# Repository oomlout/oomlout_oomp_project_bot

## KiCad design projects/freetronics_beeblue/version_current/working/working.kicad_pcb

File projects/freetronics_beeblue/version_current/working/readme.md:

# BeeBlue by freetronics  
This is a harvested standardized copy of a project from github.  
The original project can be found at:  
https://github.com/freetronics/BeeBlue  
Please consult that link for additional, details, files, and license information.  
Note: It was auto harvested and if the original repo had more than one board file or anything out of the ordinary the files here are likely not representative.

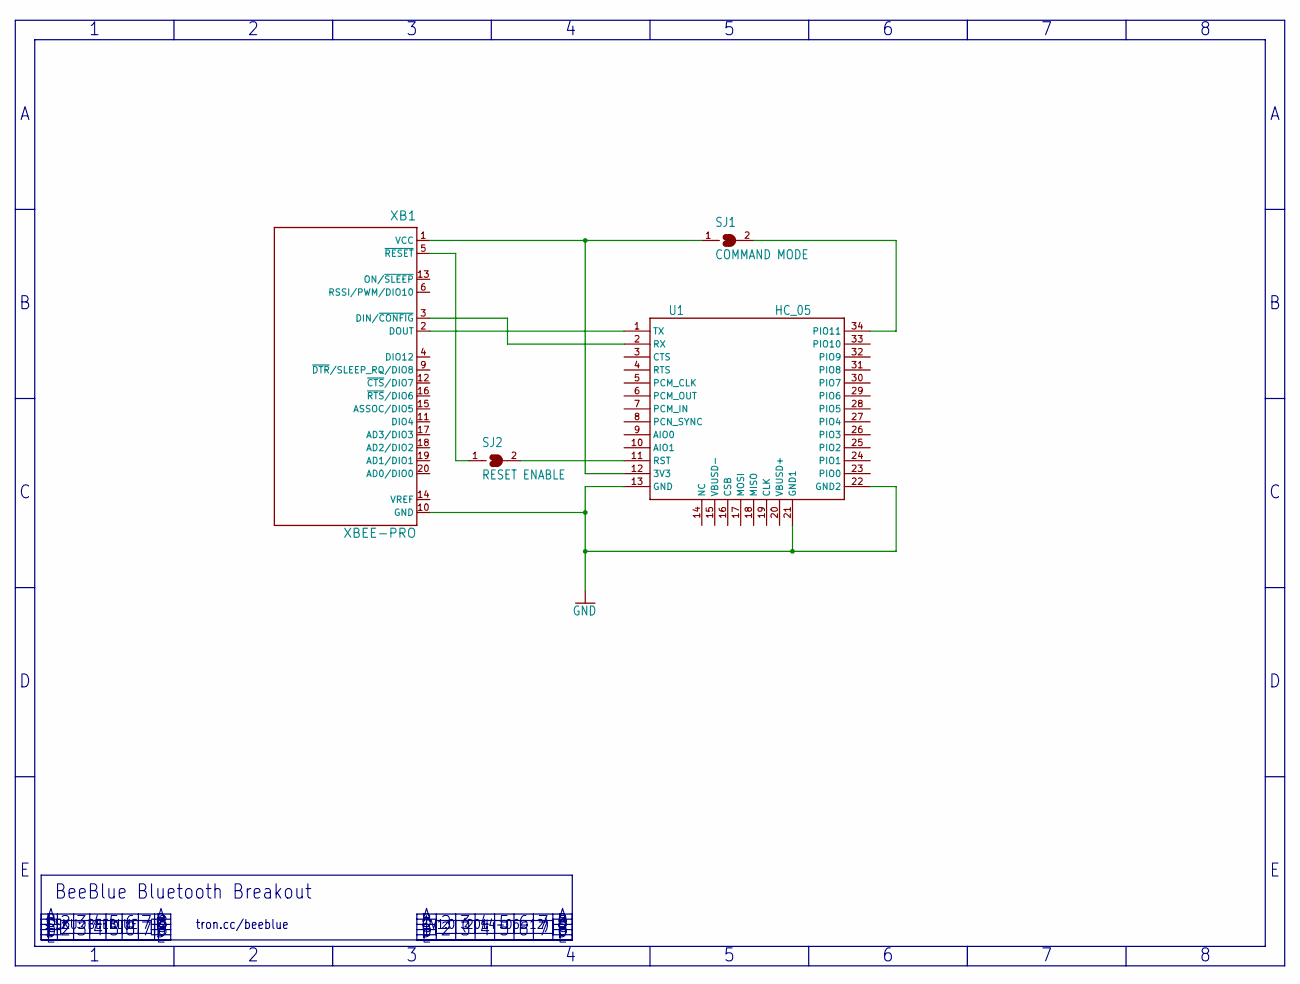
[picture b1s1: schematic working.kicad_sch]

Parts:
SJ1: COMMAND MODE; SJ
SJ2: RESET ENABLE; SJ
U1: HC_05; BLUETOOTH_SMD
XB1: XBEE-PRO

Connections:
GND: U1.13 (GND), U1.21 (GND1), U1.22 (GND2), XB1.10 (GND)
unnamed: SJ1.2, U1.34 (PIO11)
unnamed: U1.1 (TX), XB1.2 (DOUT)
unnamed: U1.2 (RX), XB1.3 (DIN/~CONFIG)
unnamed: SJ1.1, U1.12 (3V3), XB1.1 (VCC)
unnamed: SJ2.2, U1.11 (RST)
unnamed: SJ2.1, XB1.5 (~RESET)

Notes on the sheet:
tron.cc/beeblue
SKU: BEEBLUE
BeeBlue Bluetooth Breakout
V1.0 (2014-06-12)

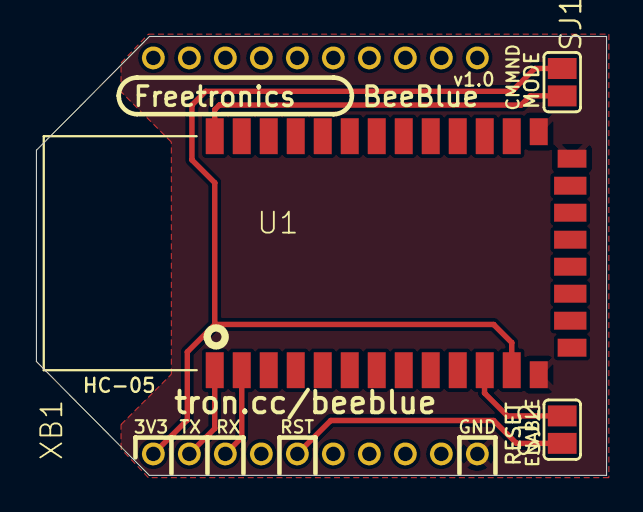
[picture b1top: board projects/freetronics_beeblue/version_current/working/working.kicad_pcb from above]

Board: 2 copper layers, 31.7 x 24.4 mm, 4 parts (0 on the bottom side), 7 nets.

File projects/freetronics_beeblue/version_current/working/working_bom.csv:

"Id";"Designator";"Footprint";"Quantity";"Designation";"Supplier and ref";
1;"XB1";"XBEE-PRO";1;"XBEE-PRO";;;
2;"U1";"BLUETOOTH_SMD";1;"HC_05";;;
3;"SJ2";"SJ";1;"RESET ENABLE";;;
4;"SJ1";"SJ";1;"COMMAND MODE";;;

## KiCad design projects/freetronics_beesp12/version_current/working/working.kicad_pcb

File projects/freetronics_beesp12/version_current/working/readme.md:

# OOMP Project  
## BEESP12  by freetronics  
  
oomp key: oomp_projects_flat_freetronics_beesp12  
(snippet of original readme)  

  full source readme at [readme_src.md](readme_src.md)  
  
source repo at: [https://github.com/freetronics/BEESP12](https://github.com/freetronics/BEESP12)  
## Board  

## Schematic  

[schematic pdf](working_schematic.pdf)  
## Images

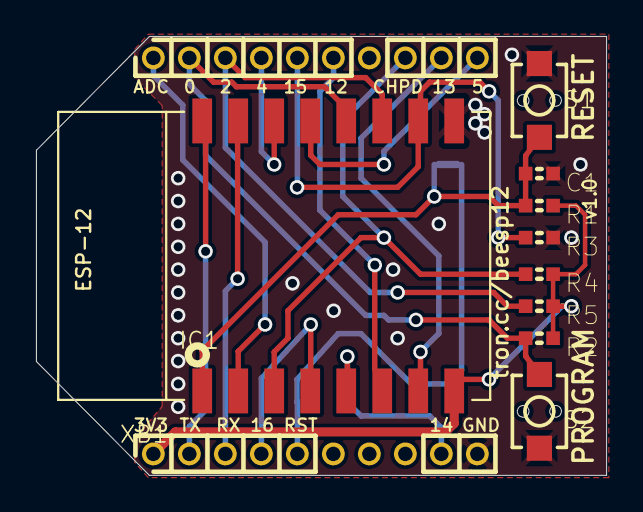
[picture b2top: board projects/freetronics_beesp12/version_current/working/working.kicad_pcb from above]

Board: 2 copper layers, 31.7 x 24.4 mm, 11 parts (1 on the bottom side), 17 nets.

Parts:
C1: 100nF; 0603
IC1: ESP12
R1, R3, R4, R5: 22K; 0603
R2: 22k; 0603
S1: RESET; TACTILE_SWITCH_SMD_2PIN_TINY
S2: PROGRAM; TACTILE_SWITCH_SMD_2PIN_TINY
SJ2: RESET LINK; SJC
XB1: XBEE-PRO

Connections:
3.3V: IC1.8, R1.2, R2.2, R4.2, R5.2, XB1.1
ADC: IC1.2, XB1.20
CH_PD: IC1.3, R4.1, XB1.13
GND: C1.2, IC1.9, R3.1, S1.2, S2.2, XB1.10
GPIO0: IC1.12, R2.1, S2.1, XB1.19
GPIO2: IC1.11, R5.1, XB1.18
GPIO4: IC1.14, XB1.17
GPIO5: IC1.13, XB1.11
GPIO12: IC1.6, XB1.15
GPIO13: IC1.7, XB1.12
GPIO14: IC1.5, XB1.9
GPIO15: IC1.10, R3.2, XB1.16
GPIO16: IC1.4, XB1.4
unnamed: C1.1, IC1.1, R1.1, S1.1, SJ2.2
RESET: SJ2.1, XB1.5
RXD: IC1.15, XB1.3
TXD: IC1.16, XB1.2

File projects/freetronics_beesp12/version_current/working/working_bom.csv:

"Id";"Designator";"Footprint";"Quantity";"Designation";"Supplier and ref";
1;"C1";"0603";1;"100nF";;;
2;"R1,R4,R5,R3";"0603";4;"22K";;;
3;"R2";"0603";1;"22k";;;
4;"S1";"TACTILE_SWITCH_SMD_2PIN_TINY";1;"RESET";;;
5;"S2";"TACTILE_SWITCH_SMD_2PIN_TINY";1;"PROGRAM";;;
6;"XB1";"XBEE-PRO";1;"XBEE-PRO";;;
7;"IC1";"ESP12";1;"ESP12";;;
8;"SJ2";"SJC";1;"RESET LINK";;;

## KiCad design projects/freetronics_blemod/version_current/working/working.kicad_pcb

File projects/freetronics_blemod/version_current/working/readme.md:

# BLEMod by freetronics  
This is a harvested standardized copy of a project from github.  
The original project can be found at:  
https://github.com/freetronics/BLEMod  
Please consult that link for additional, details, files, and license information.  
Note: It was auto harvested and if the original repo had more than one board file or anything out of the ordinary the files here are likely not representative.

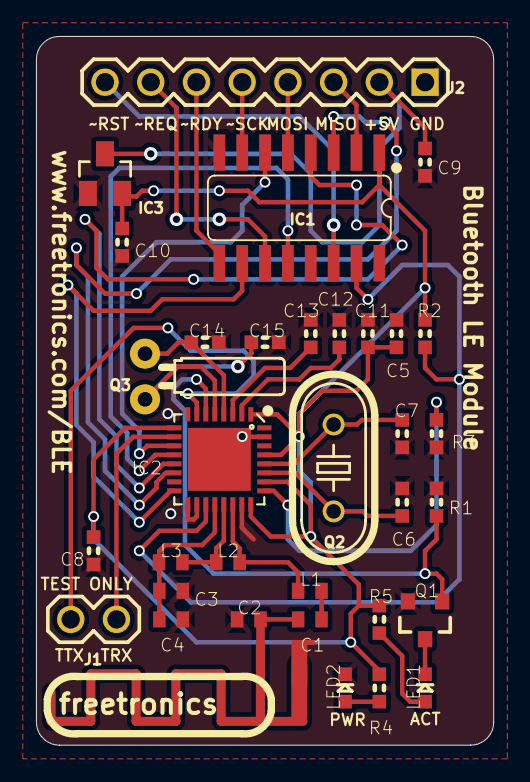
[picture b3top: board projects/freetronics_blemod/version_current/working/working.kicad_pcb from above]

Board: 2 copper layers, 25.4 x 39.4 mm, 34 parts (0 on the bottom side), 33 nets.

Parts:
ANT1: ANTENNA; RN-ANT
C1: 1.8pF; C0402
C2: 1.2pF; C0402
C3: NP; C0402
C4: 2.2nF; C0402
C5: 1nF; 0603
C6, C7: 27pF; 0603
C8, C11, C12: 100nF; 0603
C9, C10: 1µF; 0603
C13: 33nF; 0603
C14, C15: 18pF; 0603
IC1: HEF4050BT; SO16
IC2: NRF8001; FITNESSDEVICE_QFN-32
IC3: MCP1700T-3002E; SOT23
J1: Debug/Test UART; 1X02
J2: Interface; 1X08
L1: 3.9nH; C0402
L2: 8.2nH; C0402
L3: 5.6nH; C0402
LED1: Activity; LED-0603
LED2: Power; LED-0603
Q1: 2N7002; SOT23-3
Q2: 16 MHz; HC49U-V
Q3: 32768 Hz; TC26H
R1: 100kΩ; 0603
R2: 10kΩ; 0603
R3: 22kΩ 1%; 0603
R4, R5: 1kΩ; 0603

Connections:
+3.0V: C5.2, C8.2, C10.2, C11.2, IC1.1, IC2.1, IC2.9, IC2.24, IC2.26, IC2.29, IC3.2, R2.1, R4.2, R5.1
+5V: C9.2, IC3.3, J2.2
ACTIVE: IC2.6, Q1.1, R1.1
ANT1: IC2.21, L2.2, L3.1
ANT2: IC2.22, L1.2, L2.1
GND: ANT1.GND, C2.1, C3.1, C4.1, C5.1, C6.1, C7.1, C8.1, C9.1, C10.1, C11.1, C12.1, C13.1, C14.1, C15.1, IC1.8, IC2.8, IC2.17, IC2.18, IC2.23, IC2.30, IC2.31, IC2.EP, IC3.1, J2.1, LED2.C, Q1.2, R1.2, R3.2
MISO: IC1.3, IC2.14
MISO_5V: IC1.2, J2.3
MOSI: IC1.4, IC2.13
MOSI_5V: IC1.5, J2.4
unnamed: C12.2, IC2.2
unnamed: C13.2, IC2.3
unnamed: IC2.25, R3.1
unnamed: C7.2, IC2.28, Q2.1
unnamed: C6.2, IC2.27, Q2.2
unnamed: C14.2, IC2.4, Q3.1
unnamed: C15.2, IC2.5, Q3.2
unnamed: ANT1.FEED, C1.1, C2.2
unnamed: C1.2, L1.1
unnamed: LED2.A, R4.1
unnamed: LED1.C, Q1.3
unnamed: LED1.A, R5.2
RXD: IC2.10, J1.1
SCK: IC1.6, IC2.11
SCK_5V: IC1.7, J2.5
TXD: IC2.7, J1.2
VDD_PA: C3.2, C4.2, IC2.20, L3.2
~RDY_5V: IC1.9, J2.6
~RDY: IC1.10, IC2.16
~REQ_5V: IC1.11, J2.7
~REQ: IC1.12, IC2.12
~RESET_5V: IC1.14, J2.8
~RESET: IC1.15, IC2.19, R2.2

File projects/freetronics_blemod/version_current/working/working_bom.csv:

"Id";"Designator";"Footprint";"Quantity";"Designation";"Supplier and ref";
1;"J2";"1X08";1;"Interface";;;
2;"C13";"0603";1;"33nF";;;
3;"C8,C12,C11";"0603";3;"100nF";;;
4;"Q1";"SOT23-3";1;"2N7002";;;
5;"C9,C10";"0603";2;"1µF";;;
6;"C2";"C0402";1;"1.2pF";;;
7;"C5";"0603";1;"1nF";;;
8;"LED1";"LED-0603";1;"Activity";;;
9;"R4,R5";"0603";2;"1kΩ";;;
10;"IC2";"FITNESSDEVICE_QFN-32";1;"NRF8001";;;
11;"C1";"C0402";1;"1.8pF";;;
12;"C4";"C0402";1;"2.2nF";;;
13;"R1";"0603";1;"100kΩ";;;
14;"Q3";"TC26H";1;"32768 Hz";;;
15;"IC3";"SOT23";1;"MCP1700T-3002E";;;
16;"C3";"C0402";1;"NP";;;
17;"C6,C7";"0603";2;"27pF";;;
18;"C14,C15";"0603";2;"18pF";;;
19;"R3";"0603";1;"22kΩ 1%";;;
20;"L3";"C0402";1;"5.6nH";;;
21;"R2";"0603";1;"10kΩ";;;
22;"J1";"1X02";1;"Debug/Test UART";;;
23;"ANT1";"RN-ANT";1;"ANTENNA";;;
24;"IC1";"SO16";1;"HEF4050BT";;;
25;"L2";"C0402";1;"8.2nH";;;
26;"L1";"C0402";1;"3.9nH";;;
27;"Q2";"HC49U-V";1;"16 MHz";;;
28;"LED2";"LED-0603";1;"Power";;;

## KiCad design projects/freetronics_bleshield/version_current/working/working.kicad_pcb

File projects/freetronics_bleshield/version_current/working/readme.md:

# BLEShield by freetronics  
This is a harvested standardized copy of a project from github.  
The original project can be found at:  
https://github.com/freetronics/BLEShield  
Please consult that link for additional, details, files, and license information.  
Note: It was auto harvested and if the original repo had more than one board file or anything out of the ordinary the files here are likely not representative.

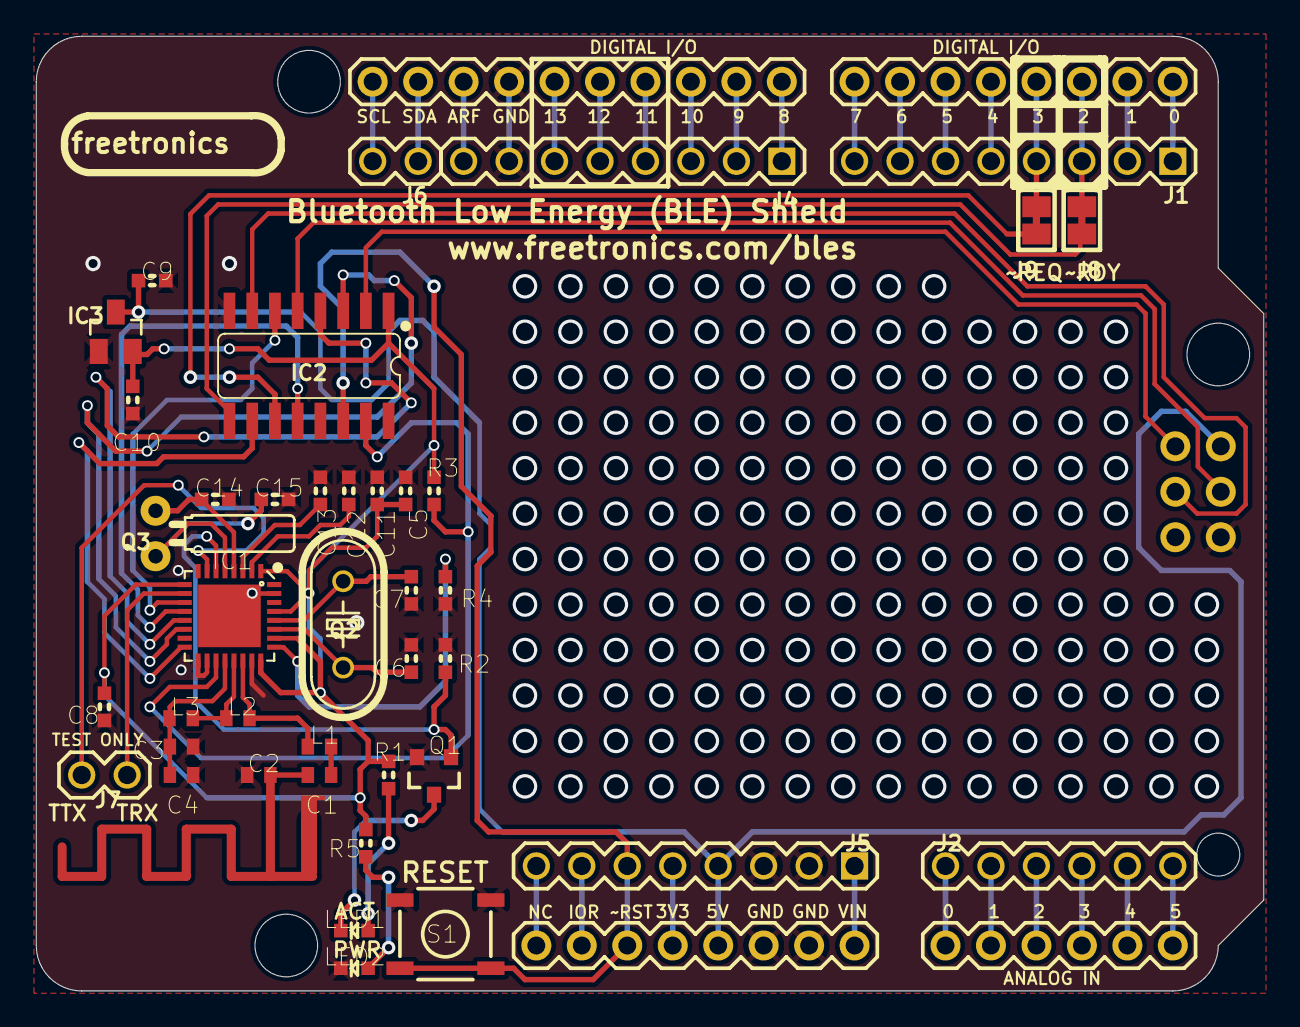
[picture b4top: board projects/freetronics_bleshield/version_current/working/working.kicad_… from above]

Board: 2 copper layers, 68.6 x 53.3 mm, 42 parts (0 on the bottom side), 60 nets.

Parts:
ANT1: ANTENNA; RN-ANT
C1: 1.8pF 0402; C0402
C2: 1.2pF 0402; C0402
C3: NP; C0402
C4: 2.2nF 0402; C0402
C5: 1nF 0603; 0603
C6, C7: 27pF 0603; 0603
C8, C11, C12: 100nF 0603; 0603
C9, C10: 1uF 0603; 0603
C13: 33nF 0603; 0603
C14, C15: 18pF 0603; 0603
IC1: NRF8001; FITNESSDEVICE_QFN-32
IC2: HEF4050BT; SO16
IC3: MCP1700T-3002E; SOT23
J1, J4, J5: 1X08
J2: 1X06
J3: ARDUINO-SHIELD_R3
J6: 1X02
J7: Debug/Test UART; 1X02
J8, J9: SJCN; SJC
L1: 3.9nH 0402; C0402
L2: 8.2nH 0402; C0402
L3: 5.6nH 0402; C0402
LED1: Activity 0603 GREEN; LED-0603
LED2: Power 0603 BLUE; LED-0603
Q1: 2N7002; SOT23-3
Q2: 16MHz HC49US; HC49U-V
Q3: 32768 Hz; TC26H
R1, R5: 1K 0603; 0603
R2: 100K 0603; 0603
R3: 10K 0603; 0603
R4: 22K 1% 0603; 0603
S1: Reset; TACTILE_SWITCH_SMD

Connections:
+3.0V: C5.2, C8.2, C10.2, C11.2, IC1.1, IC1.9, IC1.24, IC1.26, IC1.29, IC2.1, IC3.2, R1.1, R3.1, R5.2
+3.3V: J3.3V3, J5.5
+5V: C9.2, IC3.3, J3.+5V, J3.+5V@0, J5.4
A0: J2.1, J3.A0
ACTIVE: IC1.6, Q1.1, R2.1
ANT1: IC1.21, L2.2, L3.1
ANT2: IC1.22, L1.2, L2.1
C: IC2.9, J8.1
D: IC2.11, J9.1
D2: J1.3, J3.D2, J8.2
D3: J1.4, J3.D3, J9.2
GND: ANT1.GND, C2.1, C3.1, C4.1, C5.1, C6.1, C7.1, C8.1, C9.1, C10.1, C11.1, C12.1, C13.1, C14.1, C15.1, IC1.8, IC1.17, IC1.18, IC1.23, IC1.30, IC1.31, IC1.EP, IC2.8, IC3.1, J3.GND, J3.GND@0, J3.GND@1, J3.GND@2, J4.7, J5.2, J5.3, LED2.C, Q1.2, R2.2, R4.2, S1.1, S1.2
MISO: IC1.14, IC2.3
MISO_5V: IC2.2, J3.MISO
MOSI: IC1.13, IC2.4
MOSI_5V: IC2.5, J3.MOSI
unnamed: C12.2, IC1.2
unnamed: C13.2, IC1.3
unnamed: IC1.25, R4.1
unnamed: C7.2, IC1.28, Q2.1
unnamed: C6.2, IC1.27, Q2.2
unnamed: C14.2, IC1.4, Q3.1
unnamed: C15.2, IC1.5, Q3.2
unnamed: ANT1.FEED, C1.1, C2.2
unnamed: C1.2, L1.1
unnamed: LED2.A, R5.1
unnamed: LED1.C, Q1.3
unnamed: LED1.A, R1.2
unnamed: J2.2, J3.A1
unnamed: J2.3, J3.A2
unnamed: J2.4, J3.A3
unnamed: J2.5, J3.A4
unnamed: J2.6, J3.A5
unnamed: J3.RESERVED, J5.8
unnamed: J3.VIN, J5.1
unnamed: J3.IOREF, J5.7
unnamed: J1.1, J3.D0
unnamed: J1.2, J3.D1
unnamed: J1.5, J3.D4
unnamed: J1.6, J3.D5
unnamed: J1.7, J3.D6
unnamed: J1.8, J3.D7
unnamed: J3.SDA, J6.1
unnamed: J3.AREF, J4.8
unnamed: J3.D13, J4.6
unnamed: J3.D12, J4.5
unnamed: J3.SCL, J6.2
unnamed: J3.D8, J4.1
unnamed: J3.D9, J4.2
unnamed: J3.D10, J4.3
unnamed: J3.D11, J4.4
RXD: IC1.10, J7.1
SCK: IC1.11, IC2.6
SCK_5V: IC2.7, J3.SCK
TXD: IC1.7, J7.2
VDD_PA: C3.2, C4.2, IC1.20, L3.2
~RDY: IC1.16, IC2.10
~REQ: IC1.12, IC2.12
~RESET_5V: IC2.14, J3.!RESET, J5.6, S1.3, S1.4
~RESET: IC1.19, IC2.15, R3.2

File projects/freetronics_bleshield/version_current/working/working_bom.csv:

"Id";"Designator";"Footprint";"Quantity";"Designation";"Supplier and ref";
1;"L2";"C0402";1;"8.2nH 0402";;;
2;"Q1";"SOT23-3";1;"2N7002";;;
3;"R4";"0603";1;"22K 1% 0603";;;
4;"J7";"1X02";1;"Debug/Test UART";;;
5;"L3";"C0402";1;"5.6nH 0402";;;
6;"C15,C14";"0603";2;"18pF 0603";;;
7;"LED2";"LED-0603";1;"Power 0603 BLUE";;;
8;"C5";"0603";1;"1nF 0603";;;
9;"C11,C8,C12";"0603";3;"100nF 0603";;;
10;"R1,R5";"0603";2;"1K 0603";;;
11;"R3";"0603";1;"10K 0603";;;
12;"C1";"C0402";1;"1.8pF 0402";;;
13;"C2";"C0402";1;"1.2pF 0402";;;
14;"IC3";"SOT23";1;"MCP1700T-3002E";;;
15;"S1";"TACTILE_SWITCH_SMD";1;"Reset";;;
16;"J2";"1X06";1;"";;;
17;"LED1";"LED-0603";1;"Activity 0603 GREEN";;;
18;"Q2";"HC49U-V";1;"16MHz HC49US";;;
19;"Q3";"TC26H";1;"32768 Hz";;;
20;"IC1";"FITNESSDEVICE_QFN-32";1;"NRF8001";;;
21;"C9,C10";"0603";2;"1uF 0603";;;
22;"C13";"0603";1;"33nF 0603";;;
23;"R2";"0603";1;"100K 0603";;;
24;"J5,J4,J1";"1X08";3;"";;;
25;"L1";"C0402";1;"3.9nH 0402";;;
26;"IC2";"SO16";1;"HEF4050BT";;;
27;"C6,C7";"0603";2;"27pF 0603";;;
28;"J6";"1X02";1;"";;;
29;"C4";"C0402";1;"2.2nF 0402";;;
30;"ANT1";"RN-ANT";1;"ANTENNA";;;
31;"J8,J9";"SJC";2;"SJCN";;;
32;"C3";"C0402";1;"NP";;;
33;"J3";"ARDUINO-SHIELD_R3";1;"ARDUINO-SHIELD_R3";;;

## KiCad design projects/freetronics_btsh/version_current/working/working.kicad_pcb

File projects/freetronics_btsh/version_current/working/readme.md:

# BTSH by freetronics  
This is a harvested standardized copy of a project from github.  
The original project can be found at:  
https://github.com/freetronics/BTSH  
Please consult that link for additional, details, files, and license information.  
Note: It was auto harvested and if the original repo had more than one board file or anything out of the ordinary the files here are likely not representative.

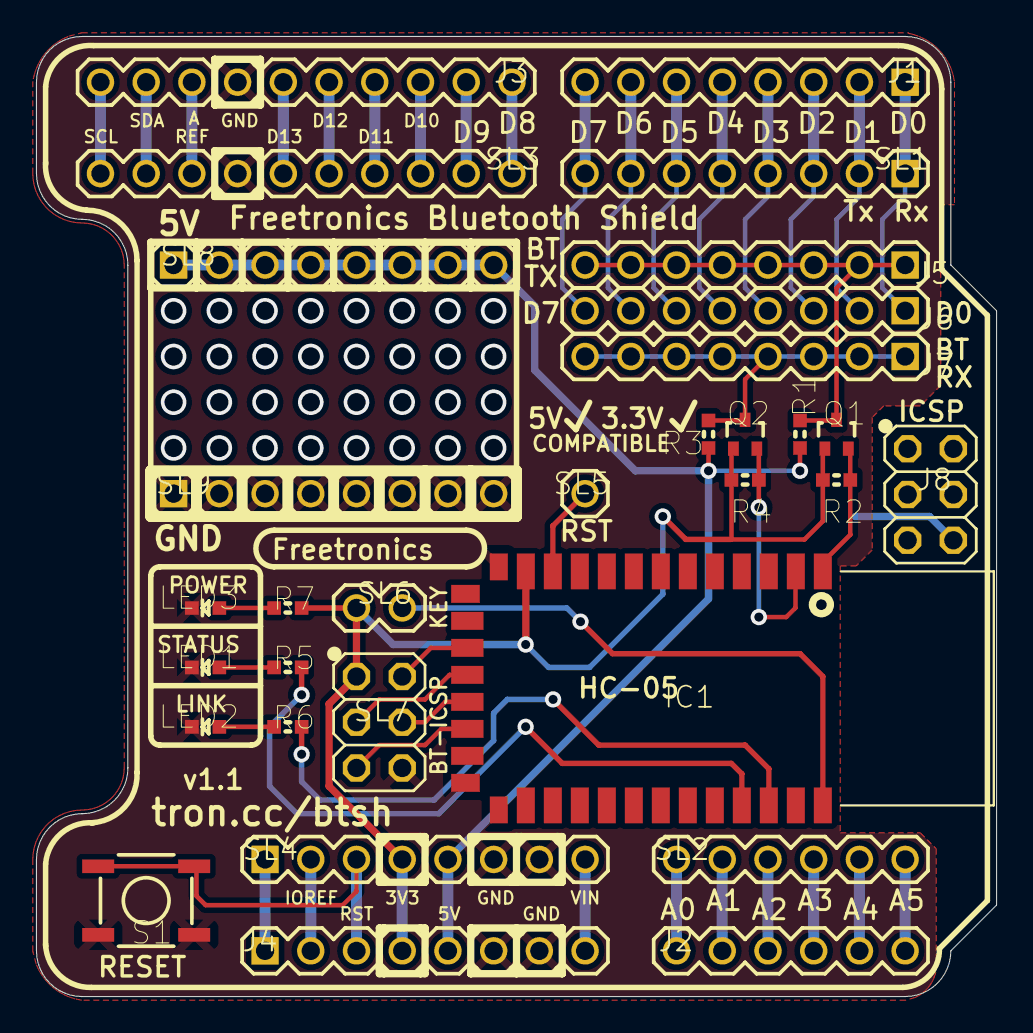
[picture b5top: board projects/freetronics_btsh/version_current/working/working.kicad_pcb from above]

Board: 2 copper layers, 53.3 x 53.3 mm, 31 parts (0 on the bottom side), 45 nets.

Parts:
IC1: HC-05; BLUETOOTH_SMD
J1, J6: Digital_0_7; 1X08
J2: Analog; 1X06
J3: Digital_8_13; 1X10
J4: Power; 1X08
J5: BT-TX; 1X08
J7: BT-RX; 1X08
J8: ICSP; 2X03PTH
LED1: YELLOW; LED-0603
LED2: GREEN; LED-0603
LED3: BLUE; LED-0603
Q1, Q2: RJU003N03 N-MOSFET; SOT32-3
R1, R2, R3, R4: 10K; 0603
R5, R6: 330R; 0603
R7: 1K; 0603
S1: RESET; TACTILE_SWITCH_SMD
SL1: Digital_0_7; 1X08
SL2: Analog; 1X06
SL3: Digital_8_13; 1X10
SL4: Power; 1X08
SL5: RESET-BT; 1X01
SL6: KEY; 1X02
SL7: ICSP-BT; 2X03PTH
SL8: 5V; 1X08
SL9: GND; 1X08

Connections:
3.3V: IC1.12, J4.4, Q1.1, Q2.1, R2.2, R4.2, R7.2, SL4.4, SL6.1, SL7.1
5V: J4.5, R1.2, R3.2, SL4.5, SL8.1, SL8.2, SL8.3, SL8.4, SL8.5, SL8.6, SL8.7, SL8.8
A0: J2.1, SL2.1
A1: J2.2, SL2.2
A2: J2.3, SL2.3
A3: J2.4, SL2.4
A4: J2.5, SL2.5
A5: J2.6, SL2.6
AREF: J3.8, SL3.8
D0_RX: J1.1, J6.1, SL1.1
D1_TX: J1.2, J6.2, SL1.2
D2: J1.3, J6.3, SL1.3
D3: J1.4, J6.4, SL1.4
D4: J1.5, J6.5, SL1.5
D5: J1.6, J6.6, SL1.6
D6: J1.7, J6.7, SL1.7
D7: J1.8, J6.8, SL1.8
D8: J3.1, SL3.1
D9: J3.2, SL3.2
D10: J3.3, SL3.3
D11_MOSI: J3.4, SL3.4
D12_MISO: J3.5, SL3.5
D13_SCK: J3.6, SL3.6
GND: IC1.13, IC1.21, IC1.22, J3.7, J4.6, J4.7, J8.6, LED1.C, LED2.C, LED3.C, S1.1, S1.2, SL3.7, SL4.6, SL4.7, SL7.6, SL9.1, SL9.2, SL9.3, SL9.4, SL9.5, SL9.6, SL9.7, SL9.8
IOREF: J4.2, SL4.2
KEY: IC1.34, SL6.2
unnamed: LED1.A, R5.1
unnamed: LED2.A, R6.1
unnamed: IC1.16, SL7.2
unnamed: IC1.31, R5.2
unnamed: IC1.32, R6.2
unnamed: LED3.A, R7.1
unnamed: IC1.11, SL5.1
unnamed: IC1.17, SL7.3
unnamed: IC1.18, SL7.4
unnamed: IC1.1, Q1.2, R2.1
unnamed: IC1.2, Q2.2, R4.1
unnamed: IC1.19, SL7.5
NC: J4.1, SL4.1
RESET: J4.3, S1.3, S1.4, SL4.3
RX: J7.1, J7.2, J7.3, J7.4, J7.5, J7.6, J7.7, J7.8, Q2.3, R3.1
SCL: J3.10, SL3.10
SDA: J3.9, SL3.9
TX: J5.1, J5.2, J5.3, J5.4, J5.5, J5.6, J5.7, J5.8, Q1.3, R1.1
VIN: J4.8, SL4.8

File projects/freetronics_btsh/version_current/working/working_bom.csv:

"Id";"Designator";"Footprint";"Quantity";"Designation";"Supplier and ref";
1;"S1";"TACTILE_SWITCH_SMD";1;"RESET";;;
2;"R2,R1,R3,R4";"0603";4;"10K";;;
3;"J3,SL3";"1X10";2;"Digital_8_13";;;
4;"J1,SL1,J6";"1X08";3;"Digital_0_7";;;
5;"SL4,J4";"1X08";2;"Power";;;
6;"LED3";"LED-0603";1;"BLUE";;;
7;"J7";"1X08";1;"BT-RX";;;
8;"LED1";"LED-0603";1;"YELLOW";;;
9;"SL5";"1X01";1;"RESET-BT";;;
10;"SL9";"1X08";1;"GND";;;
11;"SL7";"2X03PTH";1;"ICSP-BT";;;
12;"SL2,J2";"1X06";2;"Analog";;;
13;"R5,R6";"0603";2;"330R";;;
14;"R7";"0603";1;"1K";;;
15;"SL6";"1X02";1;"KEY";;;
16;"J5";"1X08";1;"BT-TX";;;
17;"IC1";"BLUETOOTH_SMD";1;"HC-05";;;
18;"LED2";"LED-0603";1;"GREEN";;;
19;"SL8";"1X08";1;"5V";;;
20;"J8";"2X03PTH";1;"ICSP";;;
21;"Q2,Q1";"SOT32-3";2;"RJU003N03 N-MOSFET";;;

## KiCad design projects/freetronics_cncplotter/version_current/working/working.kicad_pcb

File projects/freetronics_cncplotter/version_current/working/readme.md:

# CNCPlotter by freetronics  
This is a harvested standardized copy of a project from github.  
The original project can be found at:  
https://github.com/freetronics/CNCPlotter  
Please consult that link for additional, details, files, and license information.  
Note: It was auto harvested and if the original repo had more than one board file or anything out of the ordinary the files here are likely not representative.

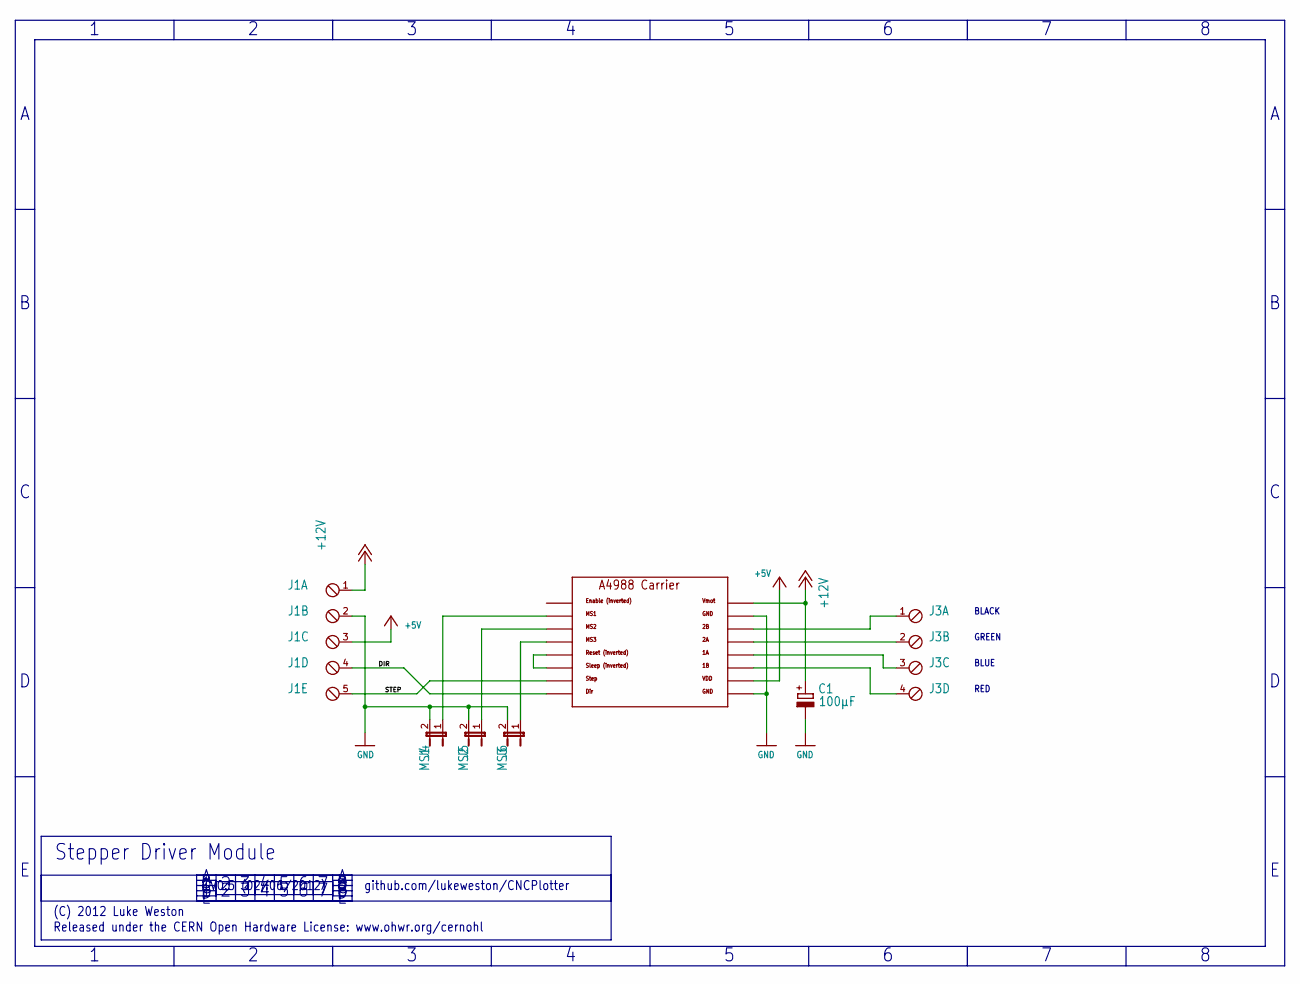
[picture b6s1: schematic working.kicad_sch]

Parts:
C1: 100µF; E2,5-6; VOLTAGE 35V
J1: Z Drive; 5POL254
J2: A4988BREAKOUT
J3: Z Motor; 4POL254
J4: MS1; JP1
J5: MS2; JP1
J6: MS3; JP1

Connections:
+5V: J1.3, J2.VDD
+12V: C1.+, J1.1, J2.VMOT
DIR: J1.4, J2.DIR
GND: C1.-, J1.2, J2.GND (GND@0), J2.GND@0 (GND@1), J4.2, J5.2, J6.2
unnamed: J2.MS1, J4.1
unnamed: J2.MS2, J5.1
unnamed: J2.MS3, J6.1
unnamed: J2.RST, J2.SLP (SLEEP)
unnamed: J2.2B, J3.1
unnamed: J2.1B, J3.4
unnamed: J2.1A, J3.3
unnamed: J2.2A, J3.2
STEP: J1.5, J2.STEP

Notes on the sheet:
Stepper Driver Module
Released under the CERN Open Hardware License: www.ohwr.org/cernohl
GREEN
(C) 2012 Luke Weston
BLACK
github.com/lukeweston/CNCPlotter
V0.5 (02/06/2012)
RED
BLUE

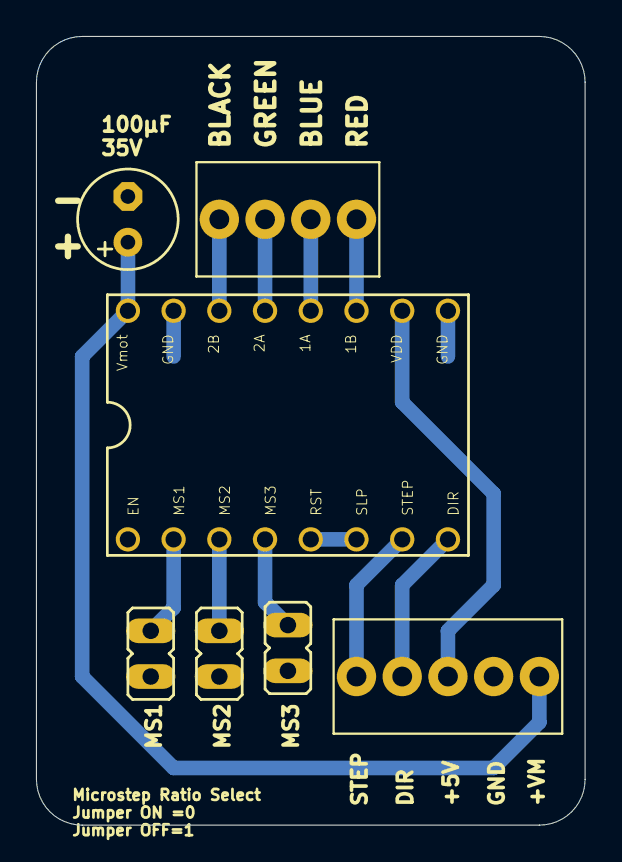
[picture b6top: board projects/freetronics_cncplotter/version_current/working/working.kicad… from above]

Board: 2 copper layers, 30.5 x 43.8 mm, 7 parts (0 on the bottom side), 13 nets.

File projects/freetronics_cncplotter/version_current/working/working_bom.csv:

"Id";"Designator";"Footprint";"Quantity";"Designation";"Supplier and ref";
1;"J4";"JP1";1;"MS1";;;
2;"J6";"JP1";1;"MS3";;;
3;"J1";"5POL254";1;"Z Drive";;;
4;"J5";"JP1";1;"MS2";;;
5;"J3";"4POL254";1;"Z Motor";;;
6;"C1";"E2,5-6";1;"100µF";;;
7;"J2";"A4988BREAKOUT";1;"A4988BREAKOUT";;;

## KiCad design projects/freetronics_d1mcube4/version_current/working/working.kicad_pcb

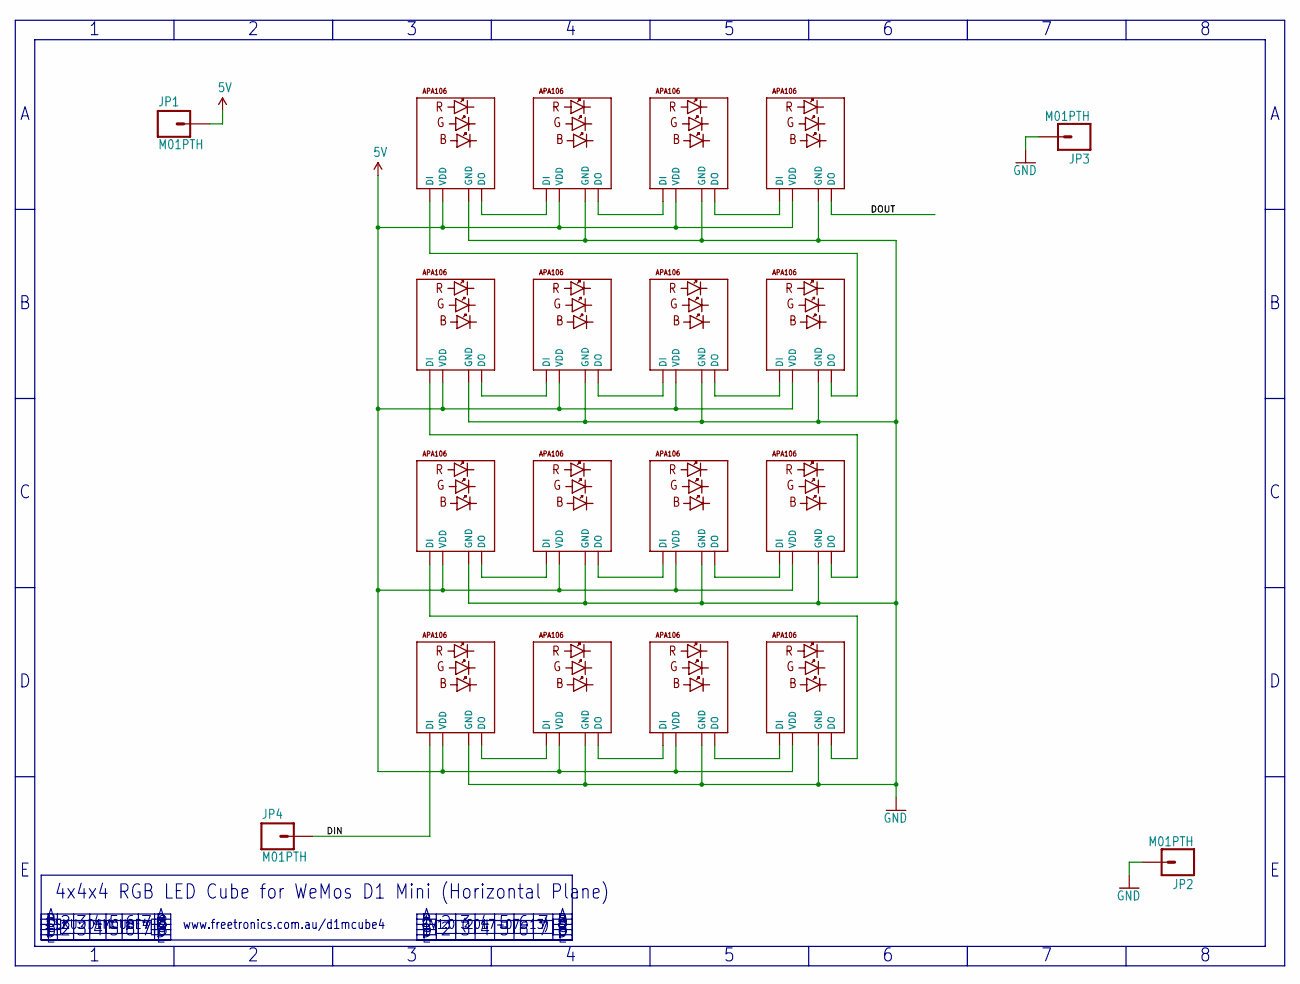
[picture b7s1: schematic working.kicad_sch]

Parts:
JP1, JP2, JP3, JP4: M01PTH; 1X01
LED1, LED2, LED3, LED4, LED5, LED6, LED7, LED8, LED9, LED10, LED11, LED12, LED13, LED14, LED15, LED16: APA106F8; LED8MMRGB

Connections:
5V: JP1.1, LED1.3 (VDD), LED2.3 (VDD), LED3.3 (VDD), LED4.3 (VDD), LED5.3 (VDD), LED6.3 (VDD), LED7.3 (VDD), LED8.3 (VDD), LED9.3 (VDD), LED10.3 (VDD), LED11.3 (VDD), LED12.3 (VDD), LED13.3 (VDD), LED14.3 (VDD), LED15.3 (VDD), LED16.3 (VDD)
DIN: JP4.1, LED1.4 (DI)
DOUT: LED16.1 (DO)
GND: JP2.1, JP3.1, LED1.2 (GND), LED2.2 (GND), LED3.2 (GND), LED4.2 (GND), LED5.2 (GND), LED6.2 (GND), LED7.2 (GND), LED8.2 (GND), LED9.2 (GND), LED10.2 (GND), LED11.2 (GND), LED12.2 (GND), LED13.2 (GND), LED14.2 (GND), LED15.2 (GND), LED16.2 (GND)
unnamed: LED1.1 (DO), LED2.4 (DI)
unnamed: LED2.1 (DO), LED3.4 (DI)
unnamed: LED3.1 (DO), LED4.4 (DI)
unnamed: LED13.1 (DO), LED14.4 (DI)
unnamed: LED14.1 (DO), LED15.4 (DI)
unnamed: LED15.1 (DO), LED16.4 (DI)
unnamed: LED9.1 (DO), LED10.4 (DI)
unnamed: LED10.1 (DO), LED11.4 (DI)
unnamed: LED11.1 (DO), LED12.4 (DI)
unnamed: LED5.1 (DO), LED6.4 (DI)
unnamed: LED6.1 (DO), LED7.4 (DI)
unnamed: LED7.1 (DO), LED8.4 (DI)
unnamed: LED12.1 (DO), LED13.4 (DI)
unnamed: LED4.1 (DO), LED5.4 (DI)
unnamed: LED8.1 (DO), LED9.4 (DI)

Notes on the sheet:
SKU: D1MCUBE4
4x4x4 RGB LED Cube for WeMos D1 Mini (Horizontal Plane)
www.freetronics.com.au/d1mcube4
V1.0 (2017-07-13)

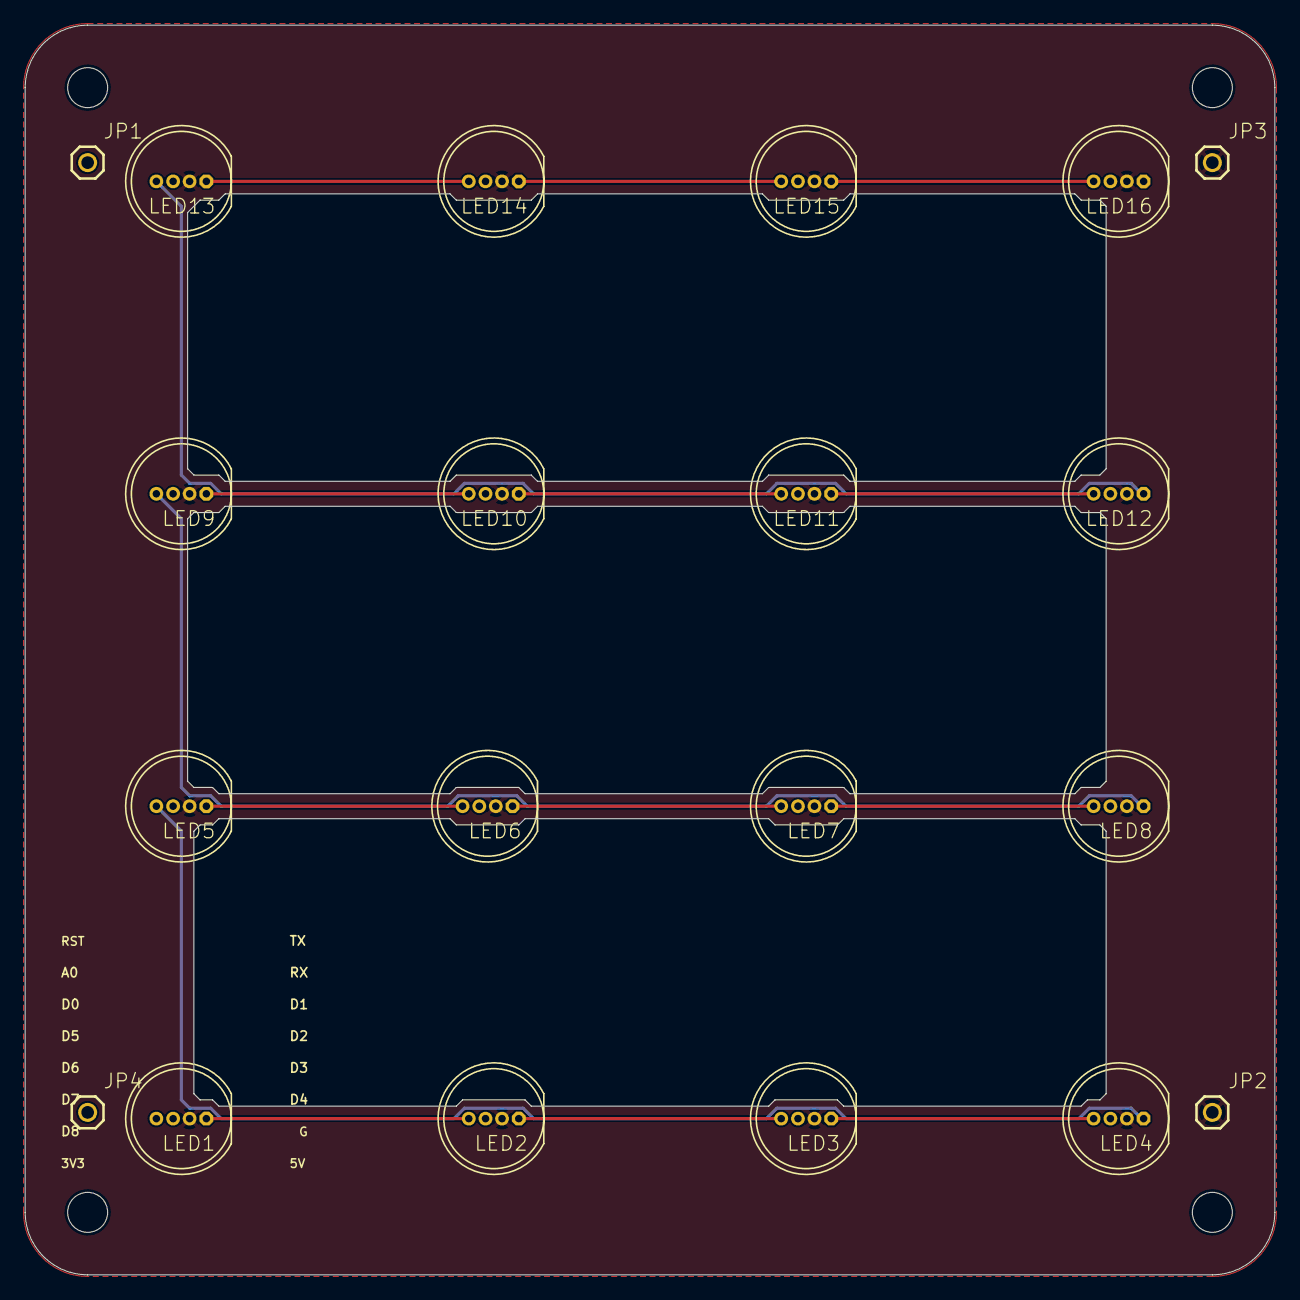
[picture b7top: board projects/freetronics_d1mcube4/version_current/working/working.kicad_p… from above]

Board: 2 copper layers, 100.0 x 100.0 mm, 24 parts (0 on the bottom side), 18 nets.

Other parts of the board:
@HOLE0, @HOLE1, @HOLE2, @HOLE3: (no value)

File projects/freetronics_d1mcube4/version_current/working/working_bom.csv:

"Id";"Designator";"Footprint";"Quantity";"Designation";"Supplier and ref";
1;"@HOLE3,@HOLE0,@HOLE2,@HOLE1";"";4;"";;;
2;"LED13,LED10,LED9,LED6,LED8,LED12,LED3,LED7,LED5,LED16,LED4,LED15,LED11,LED1,LED14,LED2";"LED8MMRGB";16;"APA106F8";;;
3;"JP1,JP4,JP3,JP2";"1X01";4;"M01PTH";;;

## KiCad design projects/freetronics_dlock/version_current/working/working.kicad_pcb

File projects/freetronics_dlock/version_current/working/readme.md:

# OOMP Project  
## DLOCK  by freetronics  
  
oomp key: oomp_projects_flat_freetronics_dlock  
(snippet of original readme)  
  
Freetronics RFID Door Lock Shield  
==================================  
Copyright 2013 Freetronics Pty Ltd    
Freetronics site:  www.freetronics.com    
Freetronics email: info@freetronics.com    
  
Based on the circuit described in the "RFID Access Control" project in  
the book "Practical Arduino", this shield allows you to control a door  
lock using an electric strike plate using a number of commonly  
available RFID reader modules.  
  
Supported reader modules include:  
  
 * ID12  
 * ID20  
 * RDM630  
 * RDM880  
 * HF MultiTag  
  
Features:  
  
 * Reset button wired through to Arduino reset pin.  
 * Blue "Arduino power on" LED with current-limiting resistor.  
 * 100nF bypass/smoothing capacitor on supply rails.  
 * Overlay guide where you need it: both top and bottom.  
  
Compatible with the Freetronics TwentyTen, Arduino Uno, Arduino  
Duemilanove, and other compatible boards based on the same header  
format.  
  
More information is available at:  
  
  http://www.freetronics.com/dlock  
  http://www.practicalarduino.com/projects/rfid-access-control  

INSTALLATION  
------------  
The design is saved as an EAGLE project. EAGLE PCB design software is  
available from www.cadsoftusa.com free for non-commercial use. To use  
this project download it and place the directory containing these files  
into the "eagle" directory on your computer. Then open EAGLE and  
navigate to Projects -> eagle -> DLOCK.  

DISTRIBUTION  
------------  
The specific terms of distribution of this project are governed by the  
license referenced below.  

LICEN  
  full source readme at [readme_src.md](readme_src.md)  
  
source repo at: [https://github.com/freetronics/DLOCK](https://github.com/freetronics/DLOCK)  
## Board  

## Schematic  

[schematic pdf](working_schematic.pdf)  
## Images

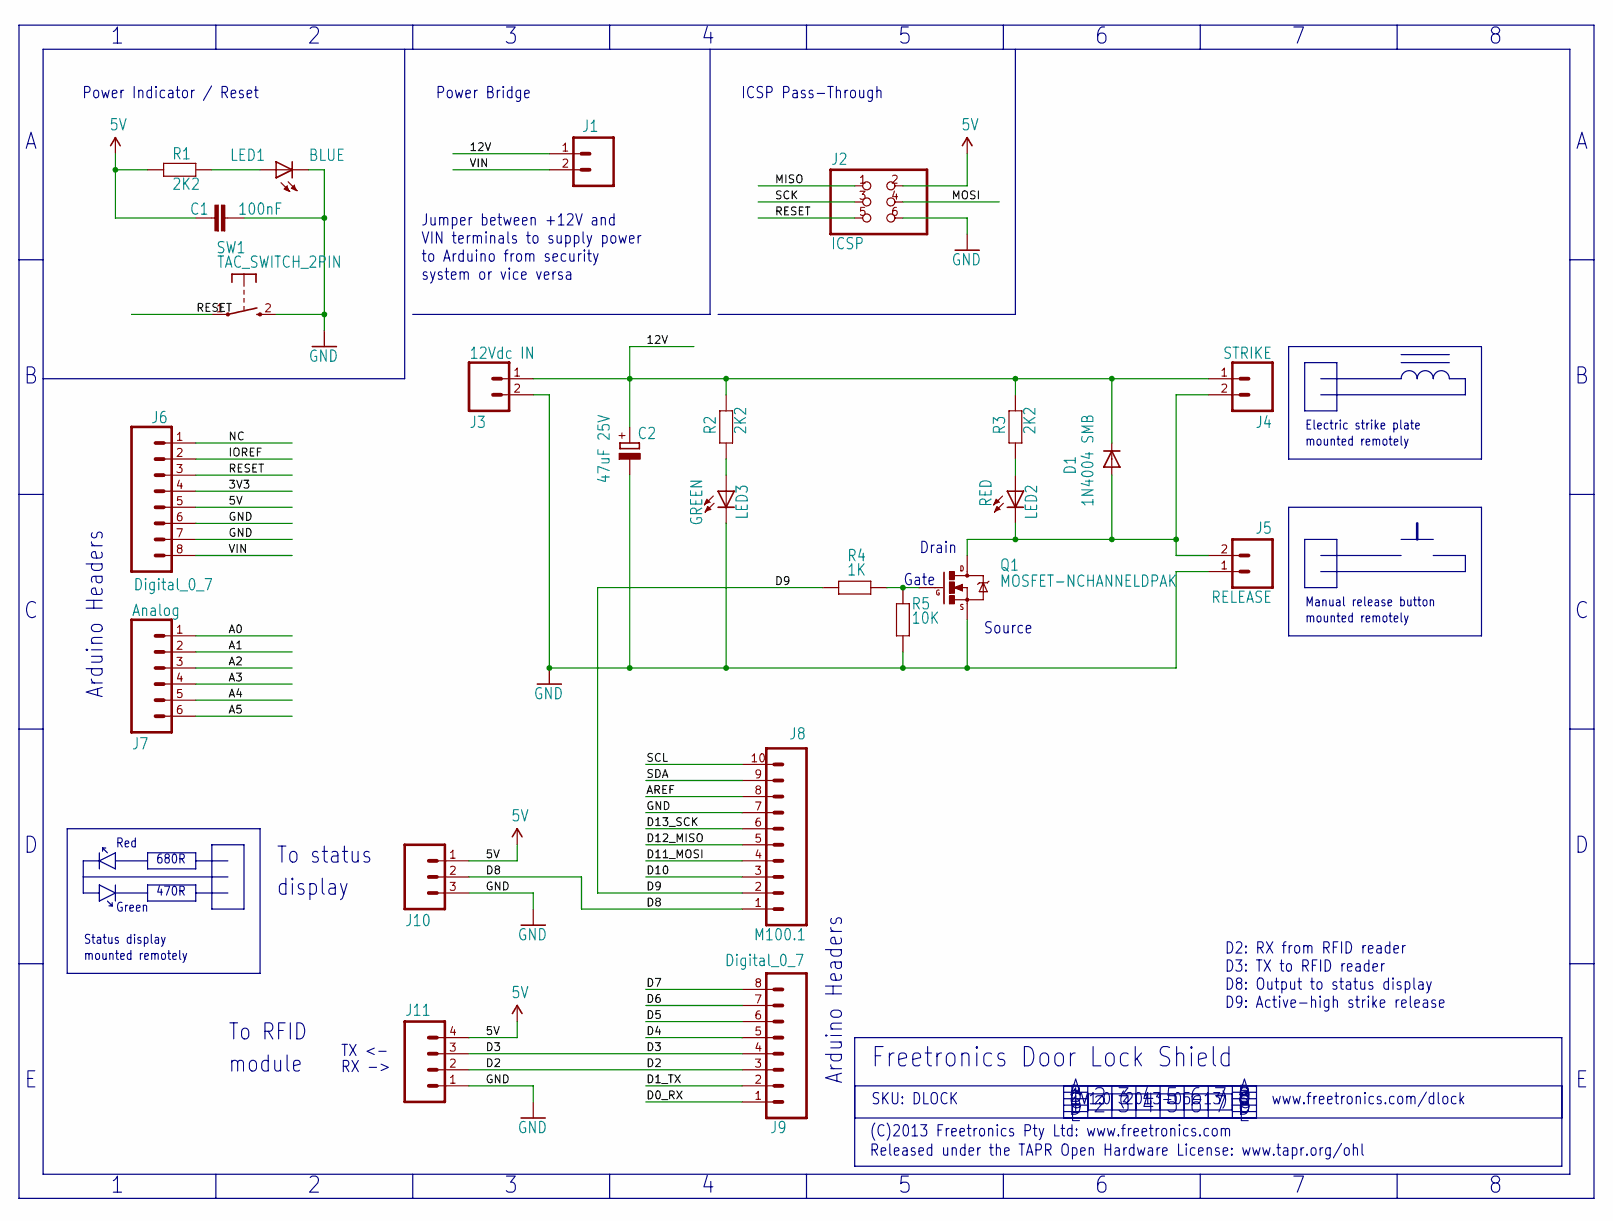
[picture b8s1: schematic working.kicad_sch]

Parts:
C1: 100nF; 0603
C2: 47uF 25V; PANASONIC_D
D1: 1N4004 SMB; SMB-DIODE
J1: M02PTH; 1X02
J2: ICSP; 2X03
J3: 12Vdc IN; SCREWTERMINAL-3.5MM-2
J4: STRIKE; SCREWTERMINAL-3.5MM-2
J5: RELEASE; 1X02
J6, J9: Digital_0_7; 1X08
J7: Analog; 1X06
J8: M100.1; 1X10
J10: M03PTH; 1X03
J11: M04PTH; 1X04
LED1: BLUE; LED-0603
LED2: RED; LED-0603
LED3: GREEN; LED-0603
Q1: MOSFET-NCHANNELDPAK; DPACK
R1, R2, R3: 2K2; 0603
R4: 1K; 0603
R5: 10K; 0603
SW1: TAC_SWITCH_2PIN; TACTILE_SWITCH_SMD_2PIN_TINY

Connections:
3V3: J6.4
5V: C1.1, J2.2, J6.5, J10.1, J11.4, R1.1
12V: C2.+, D1.C, J1.1, J3.1, J4.1, R2.2, R3.2
A0: J7.1
A1: J7.2
A2: J7.3
A3: J7.4
A4: J7.5
A5: J7.6
AREF: J8.8
D0_RX: J9.1
D1_TX: J9.2
D2: J9.3, J11.2
D3: J9.4, J11.3
D4: J9.5
D5: J9.6
D6: J9.7
D7: J9.8
D8: J8.1, J10.2
D9: J8.2, R4.2
D10: J8.3
D11_MOSI: J8.4
D12_MISO: J8.5
D13_SCK: J8.6
GND: C1.2, C2.-, J2.6, J3.2, J5.1, J6.6, J6.7, J8.7, J10.3, J11.1, LED1.C, LED3.C, Q1.3 (S), R5.1, SW1.2 (S)
IOREF: J6.2
MISO: J2.1
MOSI: J2.4
unnamed: D1.A, J4.2, J5.2, LED2.C, Q1.2 (D)
unnamed: LED2.A, R3.1
unnamed: Q1.1 (G), R4.1, R5.2
unnamed: LED3.A, R2.1
unnamed: LED1.A, R1.2
NC: J6.1
RESET: J2.5, J6.3, SW1.1
SCK: J2.3
SCL: J8.10
SDA: J8.9
VIN: J1.2, J6.8

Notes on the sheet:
To status
Status display
mounted remotely
SKU: DLOCK
Electric strike plate
Power Indicator / Reset
Gate
Source
www.freetronics.com/dlock
Manual release button
Red
(C)2013 Freetronics Pty Ltd: www.freetronics.com
display
470R
module
D2: RX from RFID reader D3: TX to RFID reader D8: Output to status display D9: Active-high strike release
TX <-
Arduino Headers
Green
V1.0 (2013-05-13)
Released under the TAPR Open Hardware License: www.tapr.org/ohl
Power Bridge
To RFID
680R
ICSP Pass-Through
Jumper between +12V and VIN terminals to supply power to Arduino from security system or vice versa
RX ->
Drain
Freetronics Door Lock Shield

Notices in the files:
projects/freetronics_beeblue/version_current/working/working.kicad_pcb:
(c)2014 Freetronics Pty Ltd
Hardware License tapr.org/OHL
projects/freetronics_beesp12/version_current/working/working.kicad_pcb:
(c)2015 Freetronics Pty Ltd
projects/freetronics_btsh/version_current/working/working.kicad_pcb:
(c) 2014 Freetronics P/L
Open Hardware License
projects/freetronics_btsh/version_current/working/working.kicad_sch:
Copyright 2014 Freetronics Pty Ltd
Released under the terms of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
projects/freetronics_d1mcube4/version_current/working/working.kicad_pcb:
(C)2017 Freetronics Pty Ltd
